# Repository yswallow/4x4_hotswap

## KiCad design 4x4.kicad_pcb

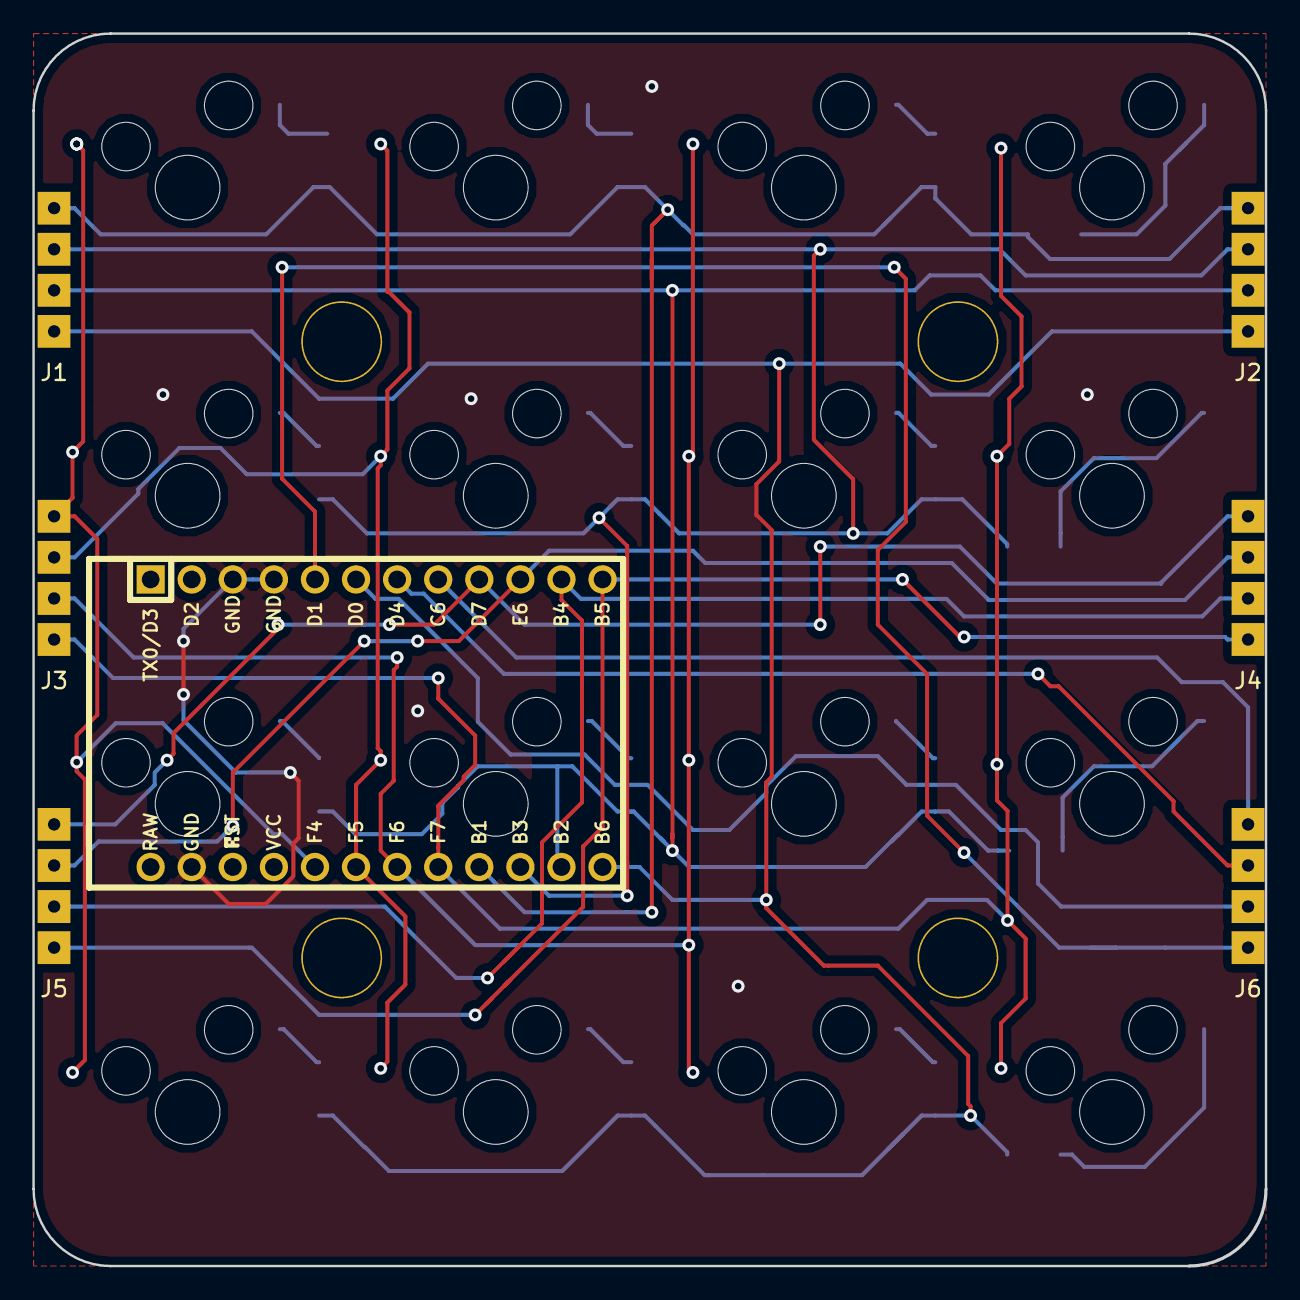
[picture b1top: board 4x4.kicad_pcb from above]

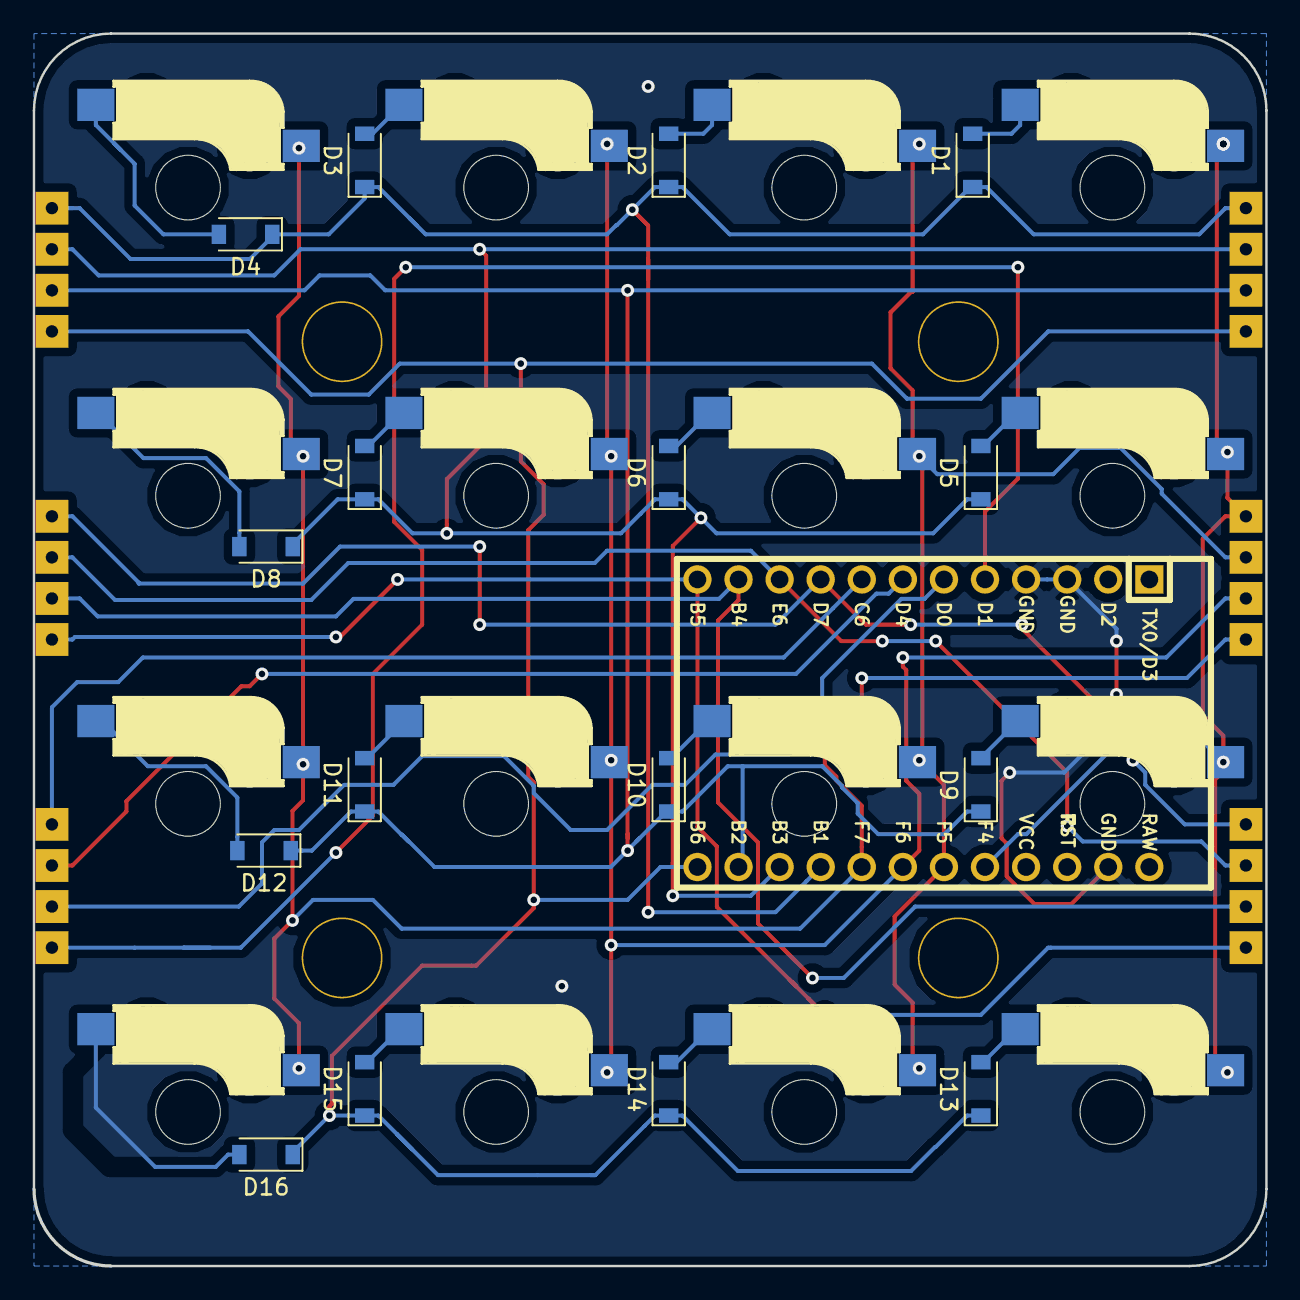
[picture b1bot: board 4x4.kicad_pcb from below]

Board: 2 copper layers, 76.2 x 76.2 mm, 43 parts (17 on the bottom side), 33 nets.

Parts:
D1, D2, D3, D4, D5, D6, D7, D8, D9, D10, D11, D12, D13, D14, D15, D16: D; D_SOD-123
J1, J2, J3, J4, J5, J6: Jumper
Ref**: Val**; HOLE
Ref**#2, Ref**#3, Ref**#4: Val**; HOLE
SW1, SW2, SW3, SW4, SW5, SW6, SW7, SW8, SW9, SW10, SW11, SW12, SW13, SW14, SW15, SW16: SW_PUSH; CherryMX_Hotswap_singleside_3pin
U1: ProMicro; FatProMicro

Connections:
GND: U1.3, U1.4, U1.23
unnamed: D1.2, SW1.2
unnamed: D2.2, SW2.2
unnamed: D3.2, SW3.2
unnamed: D4.2, SW4.2
unnamed: D5.2, SW5.2
unnamed: D6.2, SW6.2
unnamed: D7.2, SW7.2
unnamed: D8.2, SW8.2
unnamed: D9.2, SW9.2
unnamed: D10.2, SW10.2
unnamed: D11.2, SW11.2
unnamed: D12.2, SW12.2
unnamed: D13.2, SW13.2
unnamed: D14.2, SW14.2
unnamed: D15.2, SW15.2
unnamed: D16.2, SW16.2
col0: J3.1, SW1.1, SW5.1, SW9.1, SW13.1, U1.20
col1: J3.2, SW2.1, SW6.1, SW10.1, SW14.1, U1.19
col2: J3.3, SW3.1, SW7.1, SW11.1, SW15.1, U1.18
col3: J3.4, SW4.1, SW8.1, SW12.1, SW16.1, U1.17
col4: J4.1, J5.1, U1.9
col5: J4.2, J5.2, U1.10
col6: J4.3, J5.3, U1.11
col7: J4.4, J5.4, U1.12
col8: J6.1, U1.8
col9: J6.2, U1.7
col10: J6.3, U1.6
col11: J6.4, U1.5
row0: D1.1, D2.1, D3.1, D4.1, J1.1, J2.1, U1.16
row1: D5.1, D6.1, D7.1, D8.1, J1.2, J2.2, U1.15
row2: D9.1, D10.1, D11.1, D12.1, J1.3, J2.3, U1.14
row3: D13.1, D14.1, D15.1, D16.1, J1.4, J2.4, U1.13

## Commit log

2018-10-22 v0.1
2018-10-22 フットプリントを3ピンにした
